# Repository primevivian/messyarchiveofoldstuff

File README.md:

# Collection of Random Coding Projects

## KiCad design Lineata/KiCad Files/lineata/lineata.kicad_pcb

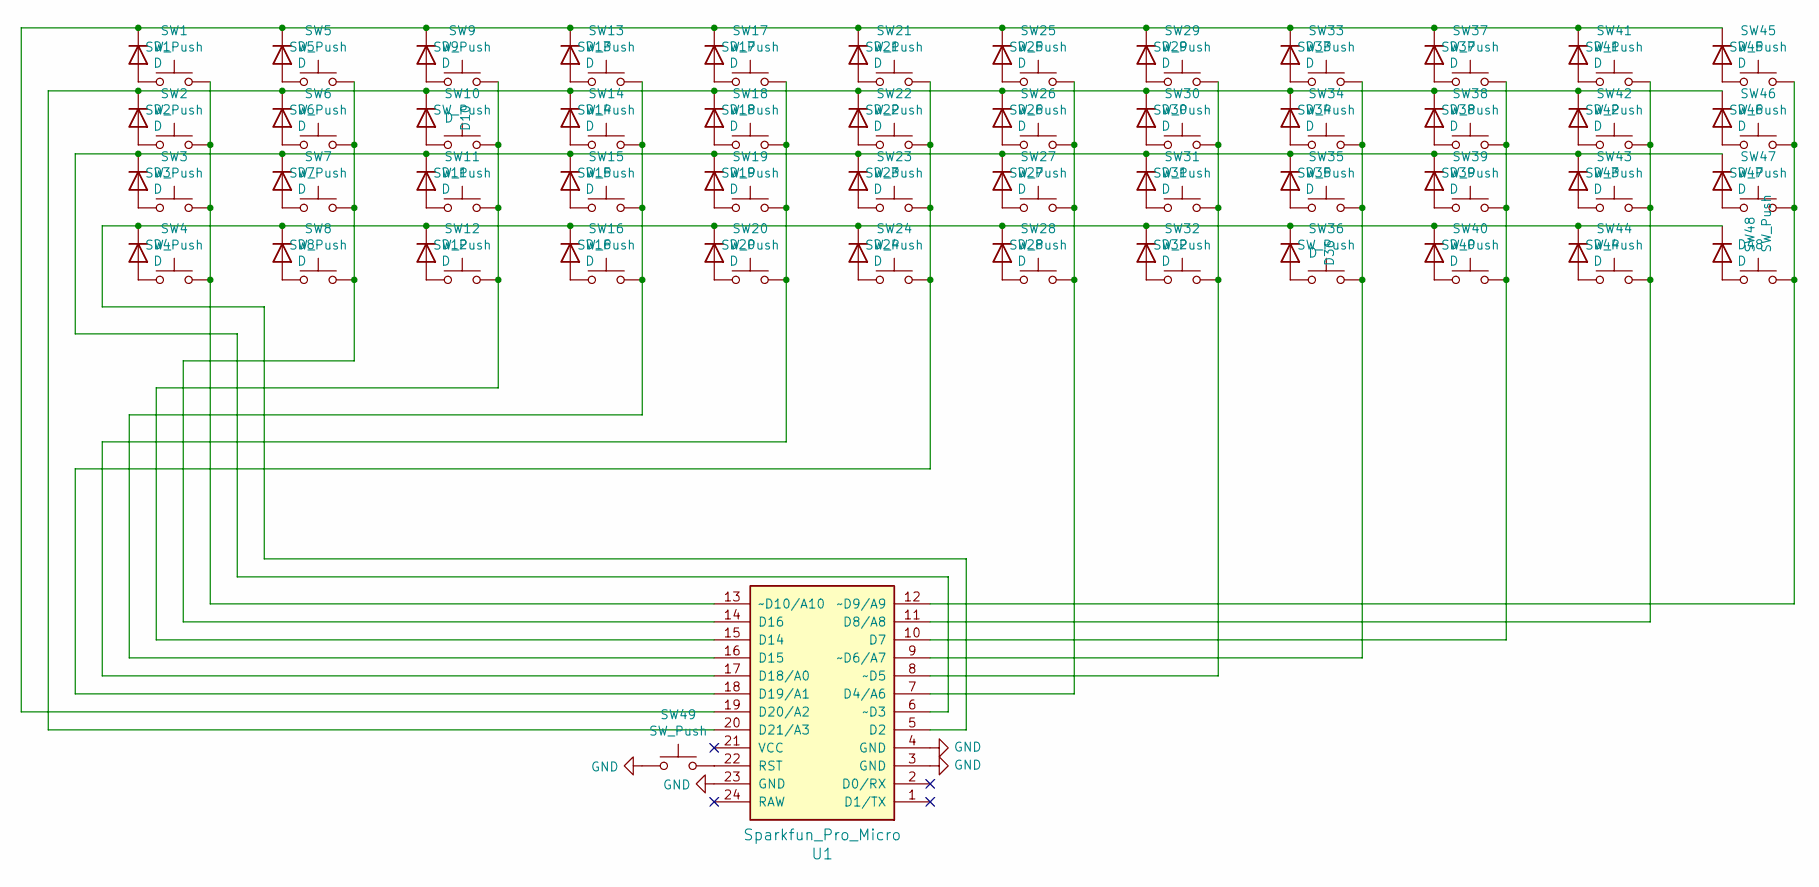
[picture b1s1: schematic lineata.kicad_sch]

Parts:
D1, D2, D3, D4, D5, D6, D7, D8, D9, D10, D11, D12, D13, D14, D15, D16, D17, D18, D19, D20, D21, D22, D23, D24, D25, D26, D27, D28, D29, D30, D31, D32, D33, D34, D35, D36, D37, D38, D39, D40, D41, D42, D43, D44, D45, D46, D47, D48: D; D_DO-35_SOD27_P7.62mm_Horizontal
SW1, SW2, SW3, SW4, SW5, SW6, SW7, SW8, SW9, SW10, SW11, SW12, SW13, SW14, SW15, SW17, SW18, SW19, SW21, SW22, SW23, SW25, SW26, SW27, SW29, SW30, SW31, SW33, SW34, SW35, SW37, SW38, SW39, SW40, SW41, SW42, SW43, SW44, SW45, SW46, SW47, SW48: SW_Push; SW_Cherry_MX_1.00u_PCB
SW16, SW36: SW_Push; SW_Cherry_MX_1.25u_PCB
SW20, SW32: SW_Push; SW_Cherry_MX_1.75u_PCB
SW24, SW28: SW_Push; SW_Cherry_MX_2.00u_PCB
SW49: SW_Push; SW_PUSH_6mm
U1: Sparkfun_Pro_Micro

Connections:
GND: SW49.1, U1.3 (GND), U1.4 (GND), U1.23 (GND)
unnamed: D1.1 (K), D5.1 (K), D9.1 (K), D13.1 (K), D17.1 (K), D21.1 (K), D25.1 (K), D29.1 (K), D33.1 (K), D37.1 (K), D41.1 (K), D45.1 (K), U1.19 (D20/A2)
unnamed: D1.2 (A), SW1.1
unnamed: D2.2 (A), SW2.1
unnamed: D3.2 (A), SW3.1
unnamed: D4.2 (A), SW4.1
unnamed: D5.2 (A), SW5.1
unnamed: D6.2 (A), SW6.1
unnamed: D7.2 (A), SW7.1
unnamed: D8.2 (A), SW8.1
unnamed: D9.2 (A), SW9.1
unnamed: D2.1 (K), D6.1 (K), D10.1 (K), D14.1 (K), D18.1 (K), D22.1 (K), D26.1 (K), D30.1 (K), D34.1 (K), D38.1 (K), D42.1 (K), D46.1 (K), U1.20 (D21/A3)
unnamed: D10.2 (A), SW10.1
unnamed: D3.1 (K), D7.1 (K), D11.1 (K), D15.1 (K), D19.1 (K), D23.1 (K), D27.1 (K), D31.1 (K), D35.1 (K), D39.1 (K), D43.1 (K), D47.1 (K), U1.6 (~D3)
unnamed: D11.2 (A), SW11.1
unnamed: D4.1 (K), D8.1 (K), D12.1 (K), D16.1 (K), D20.1 (K), D24.1 (K), D28.1 (K), D32.1 (K), D36.1 (K), D40.1 (K), D44.1 (K), D48.1 (K), U1.5 (D2)
unnamed: D12.2 (A), SW12.1
unnamed: D13.2 (A), SW13.1
unnamed: D14.2 (A), SW14.1
unnamed: D15.2 (A), SW15.1
unnamed: D16.2 (A), SW16.1
unnamed: D17.2 (A), SW17.1
unnamed: D18.2 (A), SW18.1
unnamed: D19.2 (A), SW19.1
unnamed: D20.2 (A), SW20.1
unnamed: D21.2 (A), SW21.1
unnamed: D22.2 (A), SW22.1
unnamed: D23.2 (A), SW23.1
unnamed: D24.2 (A), SW24.1
unnamed: D25.2 (A), SW25.1
unnamed: D26.2 (A), SW26.1
unnamed: D27.2 (A), SW27.1
unnamed: D28.2 (A), SW28.1
unnamed: D29.2 (A), SW29.1
unnamed: D30.2 (A), SW30.1
unnamed: D31.2 (A), SW31.1
unnamed: D32.2 (A), SW32.1
unnamed: D33.2 (A), SW33.1
unnamed: D34.2 (A), SW34.1
unnamed: D35.2 (A), SW35.1
unnamed: D36.2 (A), SW36.1
unnamed: D37.2 (A), SW37.1
unnamed: D38.2 (A), SW38.1
unnamed: D39.2 (A), SW39.1
unnamed: D40.2 (A), SW40.1
unnamed: D41.2 (A), SW41.1
unnamed: D42.2 (A), SW42.1
unnamed: D43.2 (A), SW43.1
unnamed: D44.2 (A), SW44.1
unnamed: D45.2 (A), SW45.1
unnamed: D46.2 (A), SW46.1
unnamed: D47.2 (A), SW47.1
unnamed: D48.2 (A), SW48.1
unnamed: SW1.2, SW2.2, SW3.2, SW4.2, U1.13 (~D10/A10)
unnamed: SW5.2, SW6.2, SW7.2, SW8.2, U1.14 (D16)
unnamed: SW9.2, SW10.2, SW11.2, SW12.2, U1.15 (D14)
unnamed: SW13.2, SW14.2, SW15.2, SW16.2, U1.16 (D15)
unnamed: SW17.2, SW18.2, SW19.2, SW20.2, U1.17 (D18/A0)
unnamed: SW21.2, SW22.2, SW23.2, SW24.2, U1.18 (D19/A1)
unnamed: SW25.2, SW26.2, SW27.2, SW28.2, U1.7 (D4/A6)
unnamed: SW29.2, SW30.2, SW31.2, SW32.2, U1.8 (~D5)
unnamed: SW33.2, SW34.2, SW35.2, SW36.2, U1.9 (~D6/A7)
unnamed: SW37.2, SW38.2, SW39.2, SW40.2, U1.10 (D7)
unnamed: SW41.2, SW42.2, SW43.2, SW44.2, U1.11 (D8/A8)
unnamed: SW45.2, SW46.2, SW47.2, SW48.2, U1.12 (~D9/A9)
unnamed: SW49.2, U1.22 (RST)

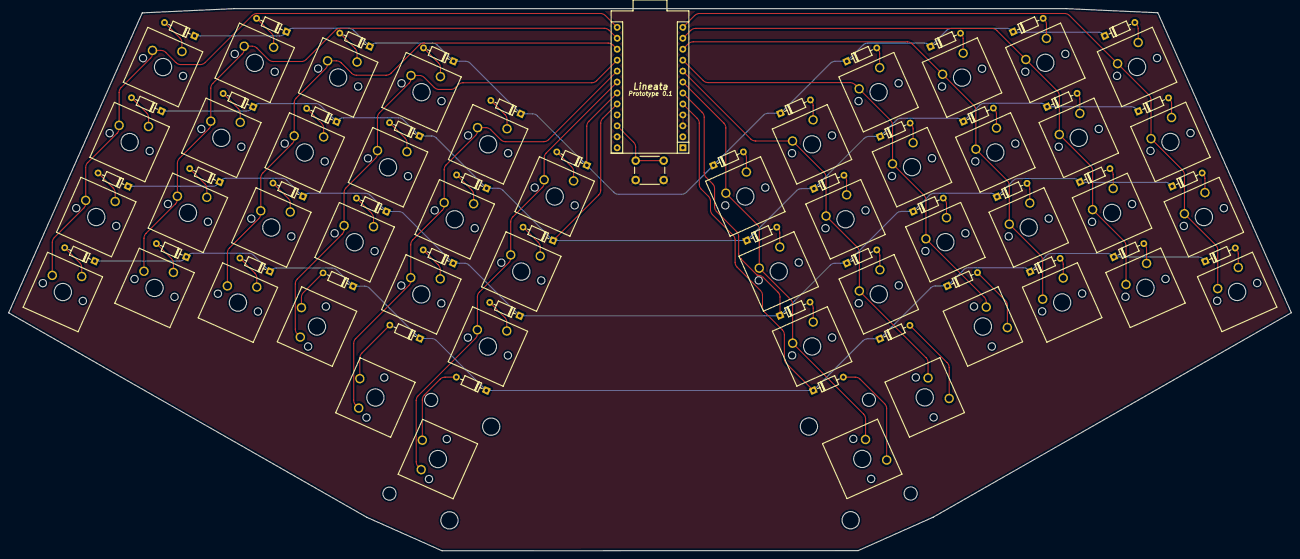
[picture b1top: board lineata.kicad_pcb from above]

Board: 2 copper layers, 297.6 x 125.8 mm, 98 parts (0 on the bottom side), 66 nets.

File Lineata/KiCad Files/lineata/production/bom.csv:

Designator,Footprint,Quantity,Value,LCSC Part #
D2,D_DO-35_SOD27_P7.62mm_Horizontal,1,D,
D3,D_DO-35_SOD27_P7.62mm_Horizontal,1,D,
D4,D_DO-35_SOD27_P7.62mm_Horizontal,1,D,
D5,D_DO-35_SOD27_P7.62mm_Horizontal,1,D,
D6,D_DO-35_SOD27_P7.62mm_Horizontal,1,D,
D7,D_DO-35_SOD27_P7.62mm_Horizontal,1,D,
D8,D_DO-35_SOD27_P7.62mm_Horizontal,1,D,
D9,D_DO-35_SOD27_P7.62mm_Horizontal,1,D,
D10,D_DO-35_SOD27_P7.62mm_Horizontal,1,D,
D12,D_DO-35_SOD27_P7.62mm_Horizontal,1,D,
D13,D_DO-35_SOD27_P7.62mm_Horizontal,1,D,
D14,D_DO-35_SOD27_P7.62mm_Horizontal,1,D,
D15,D_DO-35_SOD27_P7.62mm_Horizontal,1,D,
D16,D_DO-35_SOD27_P7.62mm_Horizontal,1,D,
D17,D_DO-35_SOD27_P7.62mm_Horizontal,1,D,
D18,D_DO-35_SOD27_P7.62mm_Horizontal,1,D,
D19,D_DO-35_SOD27_P7.62mm_Horizontal,1,D,
D20,D_DO-35_SOD27_P7.62mm_Horizontal,1,D,
D21,D_DO-35_SOD27_P7.62mm_Horizontal,1,D,
D22,D_DO-35_SOD27_P7.62mm_Horizontal,1,D,
D23,D_DO-35_SOD27_P7.62mm_Horizontal,1,D,
D24,D_DO-35_SOD27_P7.62mm_Horizontal,1,D,
D25,D_DO-35_SOD27_P7.62mm_Horizontal,1,D,
D26,D_DO-35_SOD27_P7.62mm_Horizontal,1,D,
D27,D_DO-35_SOD27_P7.62mm_Horizontal,1,D,
D28,D_DO-35_SOD27_P7.62mm_Horizontal,1,D,
D29,D_DO-35_SOD27_P7.62mm_Horizontal,1,D,
D30,D_DO-35_SOD27_P7.62mm_Horizontal,1,D,
D31,D_DO-35_SOD27_P7.62mm_Horizontal,1,D,
D32,D_DO-35_SOD27_P7.62mm_Horizontal,1,D,
D33,D_DO-35_SOD27_P7.62mm_Horizontal,1,D,
D34,D_DO-35_SOD27_P7.62mm_Horizontal,1,D,
D35,D_DO-35_SOD27_P7.62mm_Horizontal,1,D,
D36,D_DO-35_SOD27_P7.62mm_Horizontal,1,D,
D37,D_DO-35_SOD27_P7.62mm_Horizontal,1,D,
D38,D_DO-35_SOD27_P7.62mm_Horizontal,1,D,
D39,D_DO-35_SOD27_P7.62mm_Horizontal,1,D,
D40,D_DO-35_SOD27_P7.62mm_Horizontal,1,D,
D41,D_DO-35_SOD27_P7.62mm_Horizontal,1,D,
D42,D_DO-35_SOD27_P7.62mm_Horizontal,1,D,
D43,D_DO-35_SOD27_P7.62mm_Horizontal,1,D,
D44,D_DO-35_SOD27_P7.62mm_Horizontal,1,D,
D45,D_DO-35_SOD27_P7.62mm_Horizontal,1,D,
D46,D_DO-35_SOD27_P7.62mm_Horizontal,1,D,
D47,D_DO-35_SOD27_P7.62mm_Horizontal,1,D,
D48,D_DO-35_SOD27_P7.62mm_Horizontal,1,D,
SW2,SW_Cherry_MX_1.00u_PCB,1,SW_Push,
SW3,SW_Cherry_MX_1.00u_PCB,1,SW_Push,
SW4,SW_Cherry_MX_1.00u_PCB,1,SW_Push,
SW5,SW_Cherry_MX_1.00u_PCB,1,SW_Push,
SW6,SW_Cherry_MX_1.00u_PCB,1,SW_Push,
SW7,SW_Cherry_MX_1.00u_PCB,1,SW_Push,
SW8,SW_Cherry_MX_1.00u_PCB,1,SW_Push,
SW9,SW_Cherry_MX_1.00u_PCB,1,SW_Push,
SW10,SW_Cherry_MX_1.00u_PCB,1,SW_Push,
SW11,SW_Cherry_MX_1.00u_PCB,1,SW_Push,
SW12,SW_Cherry_MX_1.00u_PCB,1,SW_Push,
SW13,SW_Cherry_MX_1.00u_PCB,1,SW_Push,
SW14,SW_Cherry_MX_1.00u_PCB,1,SW_Push,
SW15,SW_Cherry_MX_1.00u_PCB,1,SW_Push,
SW17,SW_Cherry_MX_1.00u_PCB,1,SW_Push,
SW18,SW_Cherry_MX_1.00u_PCB,1,SW_Push,
SW19,SW_Cherry_MX_1.00u_PCB,1,SW_Push,
U1,Sparkfun_Pro_Micro,1,Sparkfun_Pro_Micro,
D1,D_DO-35_SOD27_P7.62mm_Horizontal,1,D,
SW1,SW_Cherry_MX_1.00u_PCB,1,SW_Push,
SW20,SW_Cherry_MX_1.75u_PCB,1,SW_Push,
SW21,SW_Cherry_MX_1.00u_PCB,1,SW_Push,
SW22,SW_Cherry_MX_1.00u_PCB,1,SW_Push,
SW23,SW_Cherry_MX_1.00u_PCB,1,SW_Push,
SW24,SW_Cherry_MX_2.00u_PCB,1,SW_Push,
SW25,SW_Cherry_MX_1.00u_PCB,1,SW_Push,
SW26,SW_Cherry_MX_1.00u_PCB,1,SW_Push,
SW27,SW_Cherry_MX_1.00u_PCB,1,SW_Push,
SW28,SW_Cherry_MX_2.00u_PCB,1,SW_Push,
SW29,SW_Cherry_MX_1.00u_PCB,1,SW_Push,
SW30,SW_Cherry_MX_1.00u_PCB,1,SW_Push,
SW31,SW_Cherry_MX_1.00u_PCB,1,SW_Push,
SW32,SW_Cherry_MX_1.75u_PCB,1,SW_Push,
SW33,SW_Cherry_MX_1.00u_PCB,1,SW_Push,
SW34,SW_Cherry_MX_1.00u_PCB,1,SW_Push,
SW35,SW_Cherry_MX_1.00u_PCB,1,SW_Push,
SW37,SW_Cherry_MX_1.00u_PCB,1,SW_Push,
SW38,SW_Cherry_MX_1.00u_PCB,1,SW_Push,
SW39,SW_Cherry_MX_1.00u_PCB,1,SW_Push,
SW40,SW_Cherry_MX_1.00u_PCB,1,SW_Push,
SW41,SW_Cherry_MX_1.00u_PCB,1,SW_Push,
SW42,SW_Cherry_MX_1.00u_PCB,1,SW_Push,
SW43,SW_Cherry_MX_1.00u_PCB,1,SW_Push,
SW44,SW_Cherry_MX_1.00u_PCB,1,SW_Push,
SW45,SW_Cherry_MX_1.00u_PCB,1,SW_Push,
SW46,SW_Cherry_MX_1.00u_PCB,1,SW_Push,
SW47,SW_Cherry_MX_1.00u_PCB,1,SW_Push,
SW48,SW_Cherry_MX_1.00u_PCB,1,SW_Push,
SW16,SW_Cherry_MX_1.25u_PCB,1,SW_Push,
SW36,SW_Cherry_MX_1.25u_PCB,1,SW_Push,
D11,D_DO-35_SOD27_P7.62mm_Horizontal,1,D,
SW49,SW_PUSH_6mm,1,SW_Push,

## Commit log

2024-01-24 Added README.md
2024-01-24 Added RPN Calculator Directory
2024-01-24 Added DLL Loader Directory
2024-01-24 Added Snaek Directory
2024-01-24 Updated README.md Image
2025-07-05 Adding some more old projects
